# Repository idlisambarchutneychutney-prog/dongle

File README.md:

# Dongle

A custom-designed, programmable USB dongle featuring a 9-LED grid, powered by the CH552G microcontroller. The board includes a user push-button and a USB connector.

## Features
* **Microcontroller:** CH552G 
* **Display:** 9x LEDs (D1-D9) with dedicated 330Ω resistors
* **Input:** 1x tactile push-button for user interaction
* **Custom Enclosure:** Includes a 3D-printable shell designed in Onshape

## Previews

### Schematic

### PCB Layout & Artwork

### case

## Bill of Materials (BOM)

| Designator | Component Name | Value/Specs | Footprint | LCSC Part # | Notes / Sourcing |
| :--- | :--- | :--- | :--- | :--- | :--- |
| **U1** | CH552G | 8-bit MCU, 16KB Flash | SOP-16 | `C111292` | Microcontroller |
| **C1, C2** | Ceramic Capacitor | 100nF (0.1uF) | 0603 | `C14663` | Decoupling Caps |
| **R1** | Resistor | 10kΩ | 0603 | `C25804` | Pull-up Resistor |
| **R2, R3, R4, R5, R6, R7, R8, R9, R10** | Resistor | 330Ω | 0603 | `C23138` | Current limiting for LEDs |
| **D1, D2, D3, D4, D5, D6, D7, D8, D9** | LED | Standard LED | 0805 | `C84256` | Indicator/Matrix LEDs |
| **J1** | USB Type-A Port | Male, 4-Pin, SMD | *See Footprint*| — | *Inventory Shortage* (Solder manually or substitute) |
| **SW1** | Tactile Switch | Push Button | *See Footprint*| — | *Inventory Shortage* (Solder manually or substitute) |

##  Manufacturing & Assembly
1. **PCB Fabrication:** Download the `.zip` file from the `/PCB` folder and upload it to your preferred PCB manufacturer. 
2. **Components:** All components are surface-mount (SMD) and located on the top layer to preserve the artwork on the back.
3. **3D Printing:** The enclosure can be printed in PLA, PETG, or ABS without supports. Use the `.step` file provided to slice the model in your preferred slicer.

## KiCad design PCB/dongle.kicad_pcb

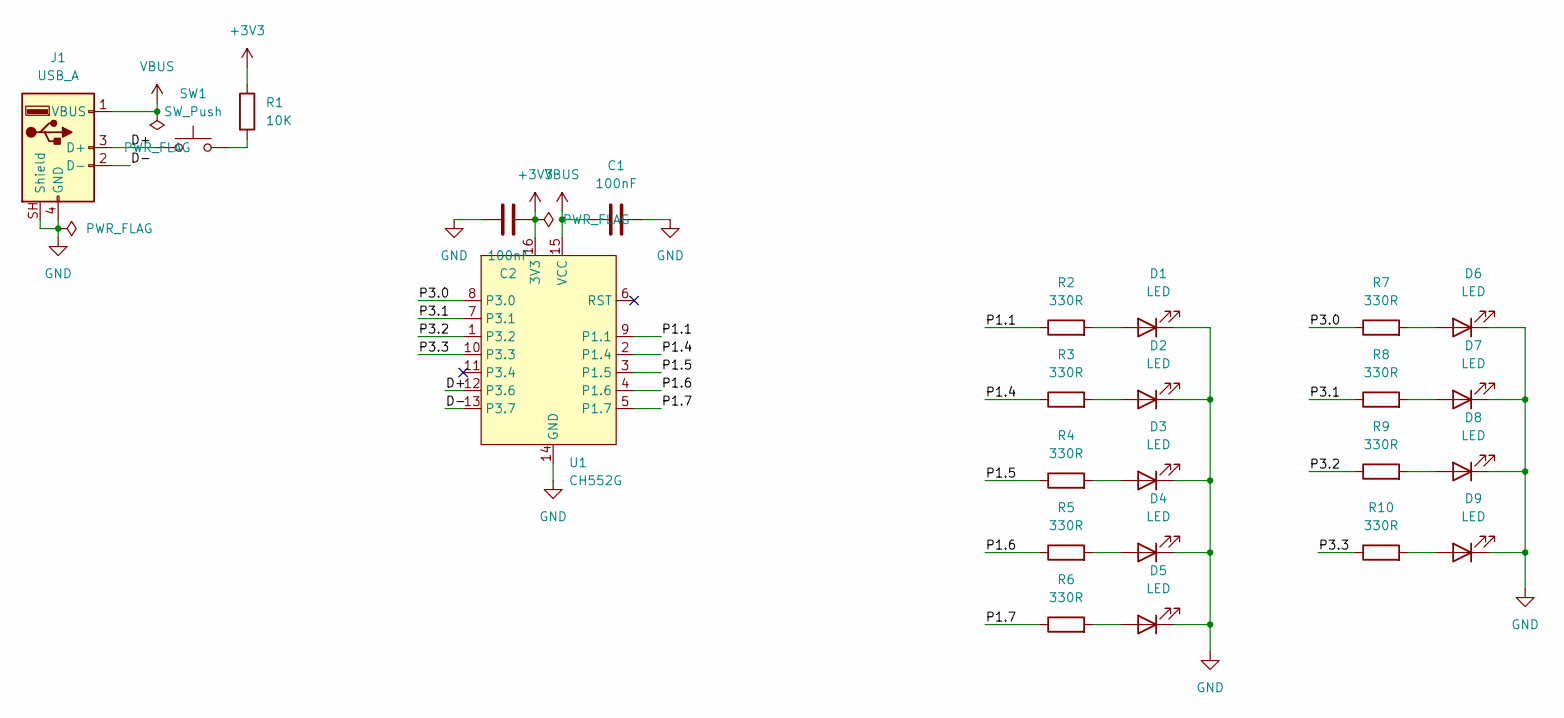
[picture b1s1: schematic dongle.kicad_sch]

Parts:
C1, C2: 100nF; C_0603_1608Metric
D1, D2, D3, D4, D5, D6, D7, D8, D9: LED; LED_0805_2012Metric
J1: USB_A; USB-A
R1: 10K; R_0603_1608Metric
R2, R3, R4, R5, R6, R7, R8, R9, R10: 330R; R_0603_1608Metric
SW1: SW_Push; SW_SPST_TS-1088-xR020
U1: CH552G; JEITA_SOIC-16_3.9x9.9mm_P1.27mm

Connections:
+3V3: C2.1, R1.1, U1.16 (3V3)
/D+: J1.3 (D+), SW1.1, U1.12 (P3.6)
/D-: J1.2 (D-), U1.13 (P3.7)
/P1.1: R2.1, U1.9 (P1.1)
/P1.4: R3.1, U1.2 (P1.4)
/P1.5: R4.1, U1.3 (P1.5)
/P1.6: R5.1, U1.4 (P1.6)
/P1.7: R6.1, U1.5 (P1.7)
/P3.0: R7.1, U1.8 (P3.0)
/P3.1: R8.1, U1.7 (P3.1)
/P3.2: R9.1, U1.1 (P3.2)
/P3.3: R10.1, U1.10 (P3.3)
GND: C1.2, C2.2, D1.1 (K), D2.1 (K), D3.1 (K), D4.1 (K), D5.1 (K), D6.1 (K), D7.1 (K), D8.1 (K), D9.1 (K), J1.4 (GND), J1.SH (Shield), U1.14 (GND)
unnamed: D1.2 (A), R2.2
unnamed: D2.2 (A), R3.2
unnamed: D3.2 (A), R4.2
unnamed: D4.2 (A), R5.2
unnamed: D5.2 (A), R6.2
unnamed: D6.2 (A), R7.2
unnamed: D7.2 (A), R8.2
unnamed: D8.2 (A), R9.2
unnamed: D9.2 (A), R10.2
unnamed: R1.2, SW1.2
VBUS: C1.1, J1.1 (VBUS), U1.15 (VCC)

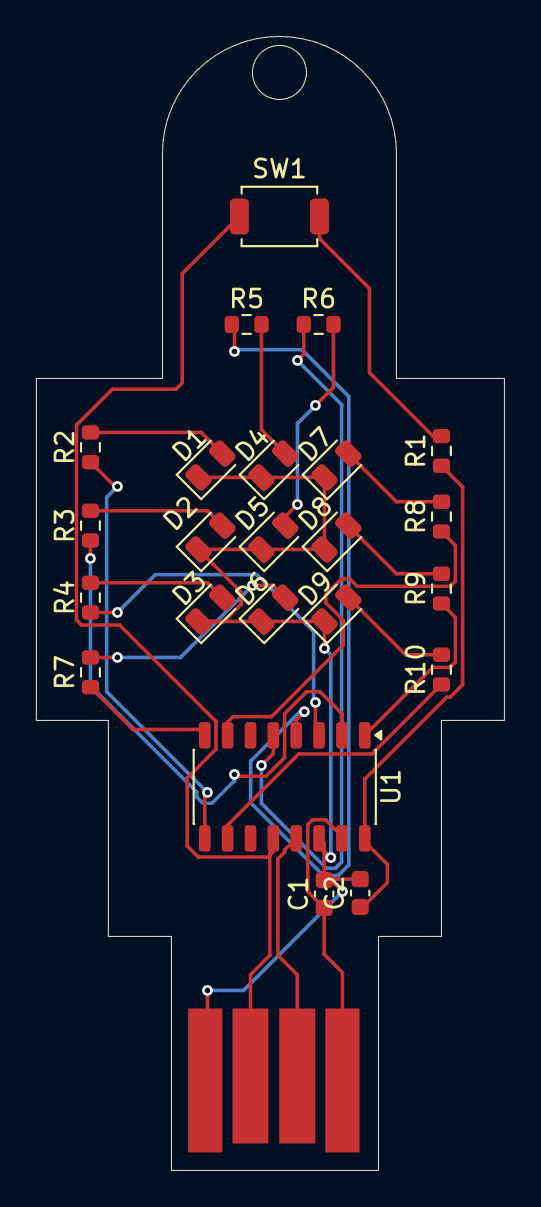
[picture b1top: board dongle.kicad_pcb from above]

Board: 2 copper layers, 26.0 x 63.0 mm, 24 parts (0 on the bottom side), 24 nets.

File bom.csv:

"Reference","Qty","Value","Footprint","Description"
"C1,C2","2","100nF","Capacitor_SMD:C_0603_1608Metric","Unpolarized capacitor"
"D1,D2,D3,D4,D5,D6,D7,D8,D9","9","LED","LED_SMD:LED_0805_2012Metric","Light emitting diode"
"J1","1","USB_A","CH552G:USB-A","USB Type A connector"
"R1","1","10K","Resistor_SMD:R_0603_1608Metric","Resistor"
"R2,R3,R4,R5,R6,R7,R8,R9,R10","9","330R","Resistor_SMD:R_0603_1608Metric","Resistor"
"SW1","1","SW_Push","Button_Switch_SMD:SW_SPST_TS-1088-xR020","Push button switch, generic, two pins"
"U1","1","CH552G","Package_SO:JEITA_SOIC-16_3.9x9.9mm_P1.27mm",""
